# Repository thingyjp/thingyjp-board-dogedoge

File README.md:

# DogeDoge Allwinner V3S SoM

## What

DogeDoge is a *complete* Linux system on a module. Complete meaning it can boot to a shell if you put power into it.

This repo contains (maybe not right now):

- Kicad files for the core board.
- Kicad files for a test/programming jig.
- Kicad files for one or more wifi modules that work with the thingy.jp middleware. 
- Makefiles, configs etc to create buildroot based firmware images with the thingy.jp middleware for wifi configuration, OTA updates etc.
- Makefiles, configs etc to create a buildroot based sd-card image for automated testing and writing the initial firmware in a jig.

## Why

People continue to use complete garbage to put together both commercial and hobby network enabled, IoT, things.

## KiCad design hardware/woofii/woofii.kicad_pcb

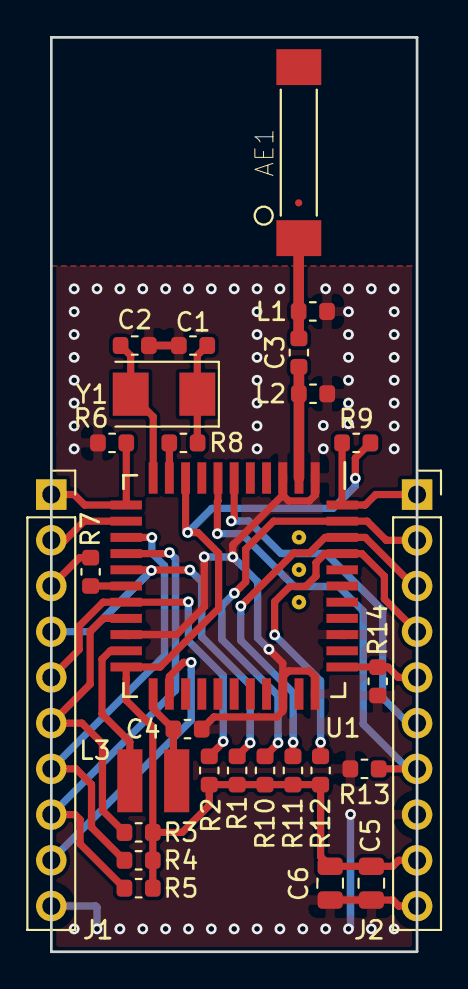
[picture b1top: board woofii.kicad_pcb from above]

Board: 2 copper layers, 20.3 x 50.8 mm, 28 parts (0 on the bottom side), 26 nets.

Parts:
AE1: Antenna; SMD_ANT9520
C1, C2, C3, C4: C; C_0603_1608Metric
C5: 4.7uF; C_0805_2012Metric
C6: 0.1uF; C_0805_2012Metric
J1, J2: Conn_01x10; PinSocket_1x10_P2.54mm_Vertical
L1, L2: L; L_0603_1608Metric
L3: L; CD32
R1, R2, R3, R4, R5, R6, R7, R9, R10, R11, R12, R13, R14: R; R_0603_1608Metric
R8: 100; R_0603_1608Metric
U1: ap6212a; QFN-44_12x12_Pitch0.9mm
Y1: 26M; Crystal_SMD_5032-2Pin_5.0x3.2mm

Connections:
+3V3: C5.1, C6.1, J2.9, R1.1, R2.1, R3.1, R4.1, R5.1, R9.1, R10.1, R11.1, R12.1, U1.9, U1.22
/32khzosc: J1.9, U1.24
/bt_host_wake: J2.7, R13.1, U1.7
/bt_rxd: J2.2, R10.2, U1.43
/bt_txd: J2.3, R11.2, U1.42
/bt_wake: J2.6, U1.6
/sdio_clk: J1.3, R7.2
/sdio_cmd: J1.4, R1.2, U1.16
/sdio_d0: J1.5, R2.2, U1.18
/sdio_d1: J1.6, R3.2, U1.19
/sdio_d2: J1.7, R4.2, U1.14
/sdio_d3: J1.8, R5.2, U1.15
/~bt_cts: J2.1, R9.2, U1.44
/~bt_rst: J2.5, R14.1, U1.34
/~bt_rts: J2.4, R12.2, U1.41
/~wifi_en: J1.1, R6.1, U1.12
/~wifi_wake: J1.2, U1.13
GND: C1.2, C2.2, C4.2, C5.2, C6.2, J1.10, J2.8, J2.10, L1.2, L2.2, R6.2, R13.2, R14.2, U1.1, U1.3, U1.20, U1.31, U1.33, U1.36
unnamed: AE1.1, C3.2, L1.1
unnamed: C1.1, R8.2, Y1.1
unnamed: C2.1, U1.11, Y1.2
unnamed: C3.1, L2.1, U1.2
unnamed: C4.1, L3.1, U1.23
unnamed: L3.2, U1.21
unnamed: R7.1, U1.17
unnamed: R8.1, U1.10

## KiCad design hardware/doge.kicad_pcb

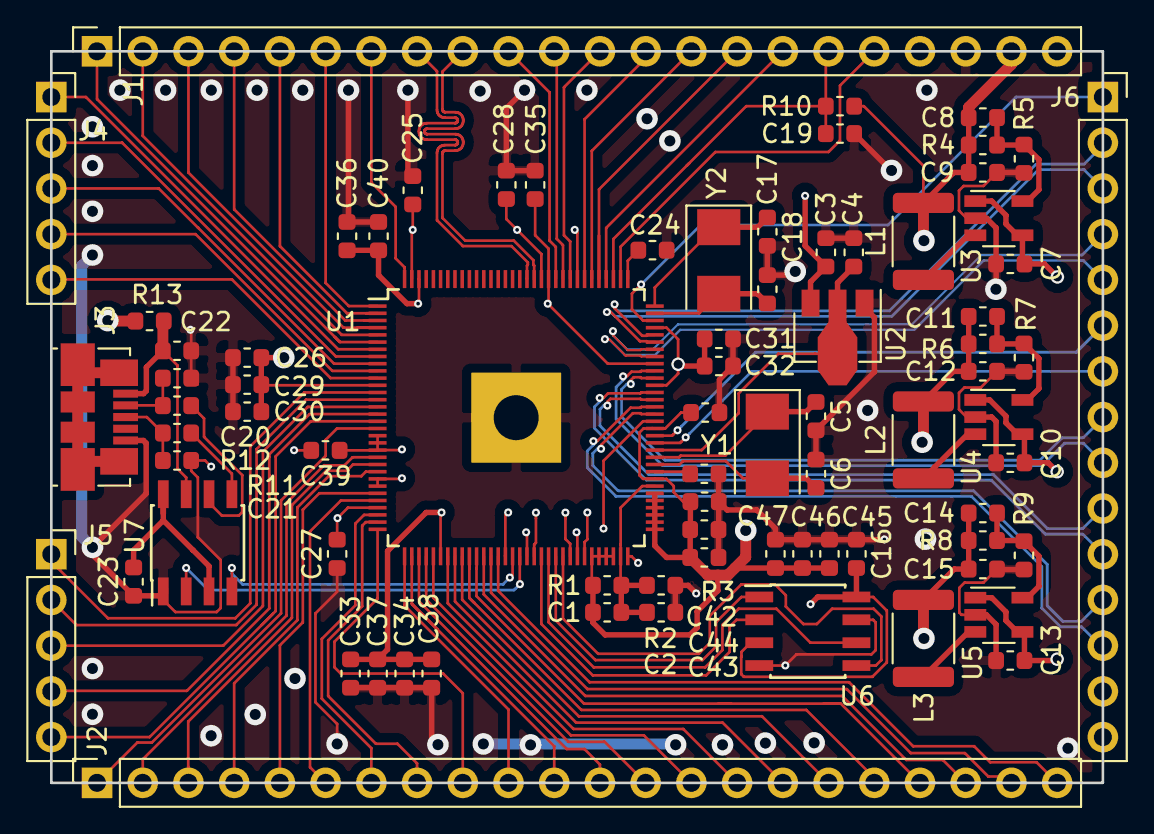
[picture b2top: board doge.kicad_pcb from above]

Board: 4 copper layers, 58.4 x 40.6 mm, 78 parts (0 on the bottom side), 94 nets.

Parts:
C1, C2, C3, C4, C5, C6, C7, C8, C9, C10, C11, C12, C13, C14, C15, C16, C17, C18, C19, C20, C21, C22, C23, C24, C25, C26, C27, C28, C29, C30, C31, C32, C33, C34, C35, C36, C37, C38, C39, C40, C41, C42, C43, C44, C45, C46, C47: C; C_0603_1608Metric
J1, J2: Conn_01x22; PinSocket_1x22_P2.54mm_Vertical
J3: USB_B_Micro; USB_Micro-B_Molex_47346-0001
J4, J5: Conn_01x05; PinSocket_1x05_P2.54mm_Vertical
J6: Conn_01x15; PinSocket_1x15_P2.54mm_Vertical
L1, L2, L3: L; L_1812_4532Metric
R1, R2, R3, R4, R5, R6, R7, R8, R9, R10, R11, R12, R13: R; R_0603_1608Metric
U1: vs3; LQFP-128_14x14mm_P0.4mm
U2: AMS1117-3.3; SOT-89-3
U3, U4, U5: RT8059GJ5; TSOT-23-5
U6: spinor; SOIC-8_3.9x4.9mm_P1.27mm
U7: ht42b534-1; SOIC-8_3.9x4.9mm_P1.27mm
Y1, Y2: Crystal; Crystal_SMD_5032-2Pin_5.0x3.2mm

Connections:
+1V2: C14.1, C15.1, C33.1, C34.1, C35.1, C36.1, C37.1, C38.1, C39.1, C40.1, L3.2, R8.1, U1.19, U1.20, U1.21, U1.25, U1.26, U1.38, U1.47, U1.51, U1.56, U1.58, U1.64, U1.80, U1.88, U1.108, U1.126
+1V8: C1.1, C11.1, C12.1, C41.1, C42.1, C43.1, C44.1, C45.1, C46.1, C47.1, L2.2, R1.1, R6.1, U1.59, U1.60, U1.61, U1.62, U1.65, U1.66, U1.67, U1.68, U1.69, U1.70, U1.72, U1.79
+3.3VA: C4.1, U1.76, U2.2
+3V3: C8.1, C9.1, C16.1, C25.1, C26.1, C27.1, C28.1, C29.1, C30.1, C31.1, C32.1, J1.21, L1.2, R4.1, R10.1, U1.12, U1.29, U1.50, U1.57, U1.85, U1.93, U1.104, U1.109, U1.127, U6.3, U6.8
+5V: C22.1, J3.1, R13.2, U7.7
/console/rx: U1.48, U7.4
/console/tx: U1.49, U7.2
/csi-ck+: J6.8, U1.86
/csi-ck-: J6.9, U1.87
/csi-d0+: J6.12, U1.81
/csi-d0-: J6.13, U1.82
/csi-d1+: J6.10, U1.83
/csi-d1-: J6.11, U1.84
/ephy_link_led: J6.7, U1.77
/ephy_rtx: J6.1, U1.94
/ephy_rx+: J6.4, U1.90
/ephy_rx-: J6.5, U1.89
/ephy_spd_led: J6.6, U1.78
/ephy_tx+: J6.2, U1.92
/ephy_tx-: J6.3, U1.91
/pb0: J2.15, U1.39
/pb1: J2.16, U1.40
/pb2: J2.17, U1.41
/pb3: J2.18, U1.42
/pb4: J2.19, U1.43
/pb5: J2.20, U1.44
/pb6: J2.21, U1.45
/pb7: J2.22, U1.46
/pe0: J2.14, U1.37
/pe1: J2.13, U1.36
/pe2: J2.12, U1.35
/pe3: J2.11, U1.34
/pe4: J2.10, U1.33
/pe5: J2.9, U1.32
/pe6: J2.8, U1.31
/pe7: J2.7, U1.30
/pe8: J2.6, U1.28
/pe9: J2.5, U1.27
/pe10: J2.4, U1.24
/pe11: J2.3, U1.23
/pe12: J2.2, U1.22
/pe13: J2.1, U1.18
/pe14: J5.5, U1.17
/pe15: J5.4, U1.16
/pe16: J5.3, U1.15
/pe17: J5.2, U1.14
/pe18: J5.1, U1.13
/pe19: J4.5, U1.11
/pe20: J4.4, U1.10
/pe21: J4.3, U1.9
/pe22: J4.2, U1.8
/pe23: J4.1, U1.7
/pe24: J1.1, U1.6
/pf0: J1.10, U1.107
/pf1: J1.11, U1.106
/pf2: J1.12, U1.105
/pf3: J1.13, U1.103
/pf4: J1.14, U1.102
/pf5: J1.15, U1.101
/pf6: J1.16, U1.100
/pg0: J1.2, U1.5
/pg1: J1.3, U1.4
/pg2: J1.4, U1.3
/pg3: J1.5, U1.2
/pg4: J1.6, U1.1
/pg5: J1.7, U1.128
/spi_clk: U1.53, U6.6
/spi_miso: U1.52, U6.2
/spi_mosi: U1.55, U6.5
/usb+: J1.8, U1.111
/usb-: J1.9, U1.110
/vcc-rtc: J1.18, U1.98
/~reset: C19.1, J1.17, R10.2, U1.99
/~spi_cs: U1.54, U6.1
GND: C2.2, C3.2, C4.2, C5.1, C6.1, C7.2, C9.2, C10.2, C12.2, C13.2, C15.2, C16.2, C17.1, C18.1, C19.2, C20.2, C21.2, C22.2, C23.1, C24.2, C25.2, C26.2, C27.2, C28.2, C29.2, C30.2, C31.2, C32.2, C33.2, C34.2, C35.2, C36.2, C37.2, C38.2, C39.2, C40.2, C41.2, C42.2, C43.2, C44.2, C45.2, C46.2, C47.2, J1.20, J3.5, R2.2, R3.2, R5.2, R7.2, R9.2, U1.129, U2.1, U3.2, U4.2, U5.2, U6.4, U6.7, U7.1
unnamed: C1.2, C2.1, R1.2, R2.1, U1.63, U1.71
unnamed: C5.2, U1.75, Y1.1
unnamed: C6.2, U1.74, Y1.2
unnamed: C8.2, R4.2, R5.1, U3.5
unnamed: C11.2, R6.2, R7.1, U4.5
unnamed: C14.2, R8.2, R9.1, U5.5
unnamed: C17.2, U1.96, Y2.1
unnamed: C18.2, U1.95, Y2.2
unnamed: C20.1, J3.2, R12.2
unnamed: C21.1, J3.3, R11.2
unnamed: C23.2, U7.3, U7.8
unnamed: C24.1, U1.97
unnamed: L1.1, U3.3
unnamed: L2.1, U4.3
unnamed: L3.1, U5.3
unnamed: R3.1, U1.73
unnamed: R11.1, U7.5
unnamed: R12.1, U7.6
VCC: C3.1, C7.1, C10.1, C13.1, J1.22, R13.1, U2.3, U3.1, U3.4, U4.1, U4.4, U5.1, U5.4

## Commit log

2018-09-13 stash
2018-09-13 status
2018-09-24 Rev 1
2018-09-26 WooFii: Clean up pcb layout.
2018-09-27 Add first version of chum
2018-09-29 Move environment stuff into a file
2018-10-01 Add some todo notes
2018-10-07 Document bug with spi nor on rev0 Fix up the reset pin on the spi nor in uboot before booting the flasher
2018-10-07 Enable hush in the firmware uboot config so the OTA script works
2018-10-07 Defconfig and env tweaks
2018-10-08 DogeDoge Rev1: switch ldo for xc6204, expose en single on buck supplies, tie enables together
2018-10-08 DogeDoge Rev1: Wire SPI NOR reset to system reset
2018-10-08 Add photos of Rev0 boards
2018-10-09 Enable wifi
2018-10-09 Update bom
2018-10-11 AP6212A tweaks
2018-10-18 Update firmware defconfig
2018-11-11 Add travis build file
2018-11-11 Put docker config into a file
